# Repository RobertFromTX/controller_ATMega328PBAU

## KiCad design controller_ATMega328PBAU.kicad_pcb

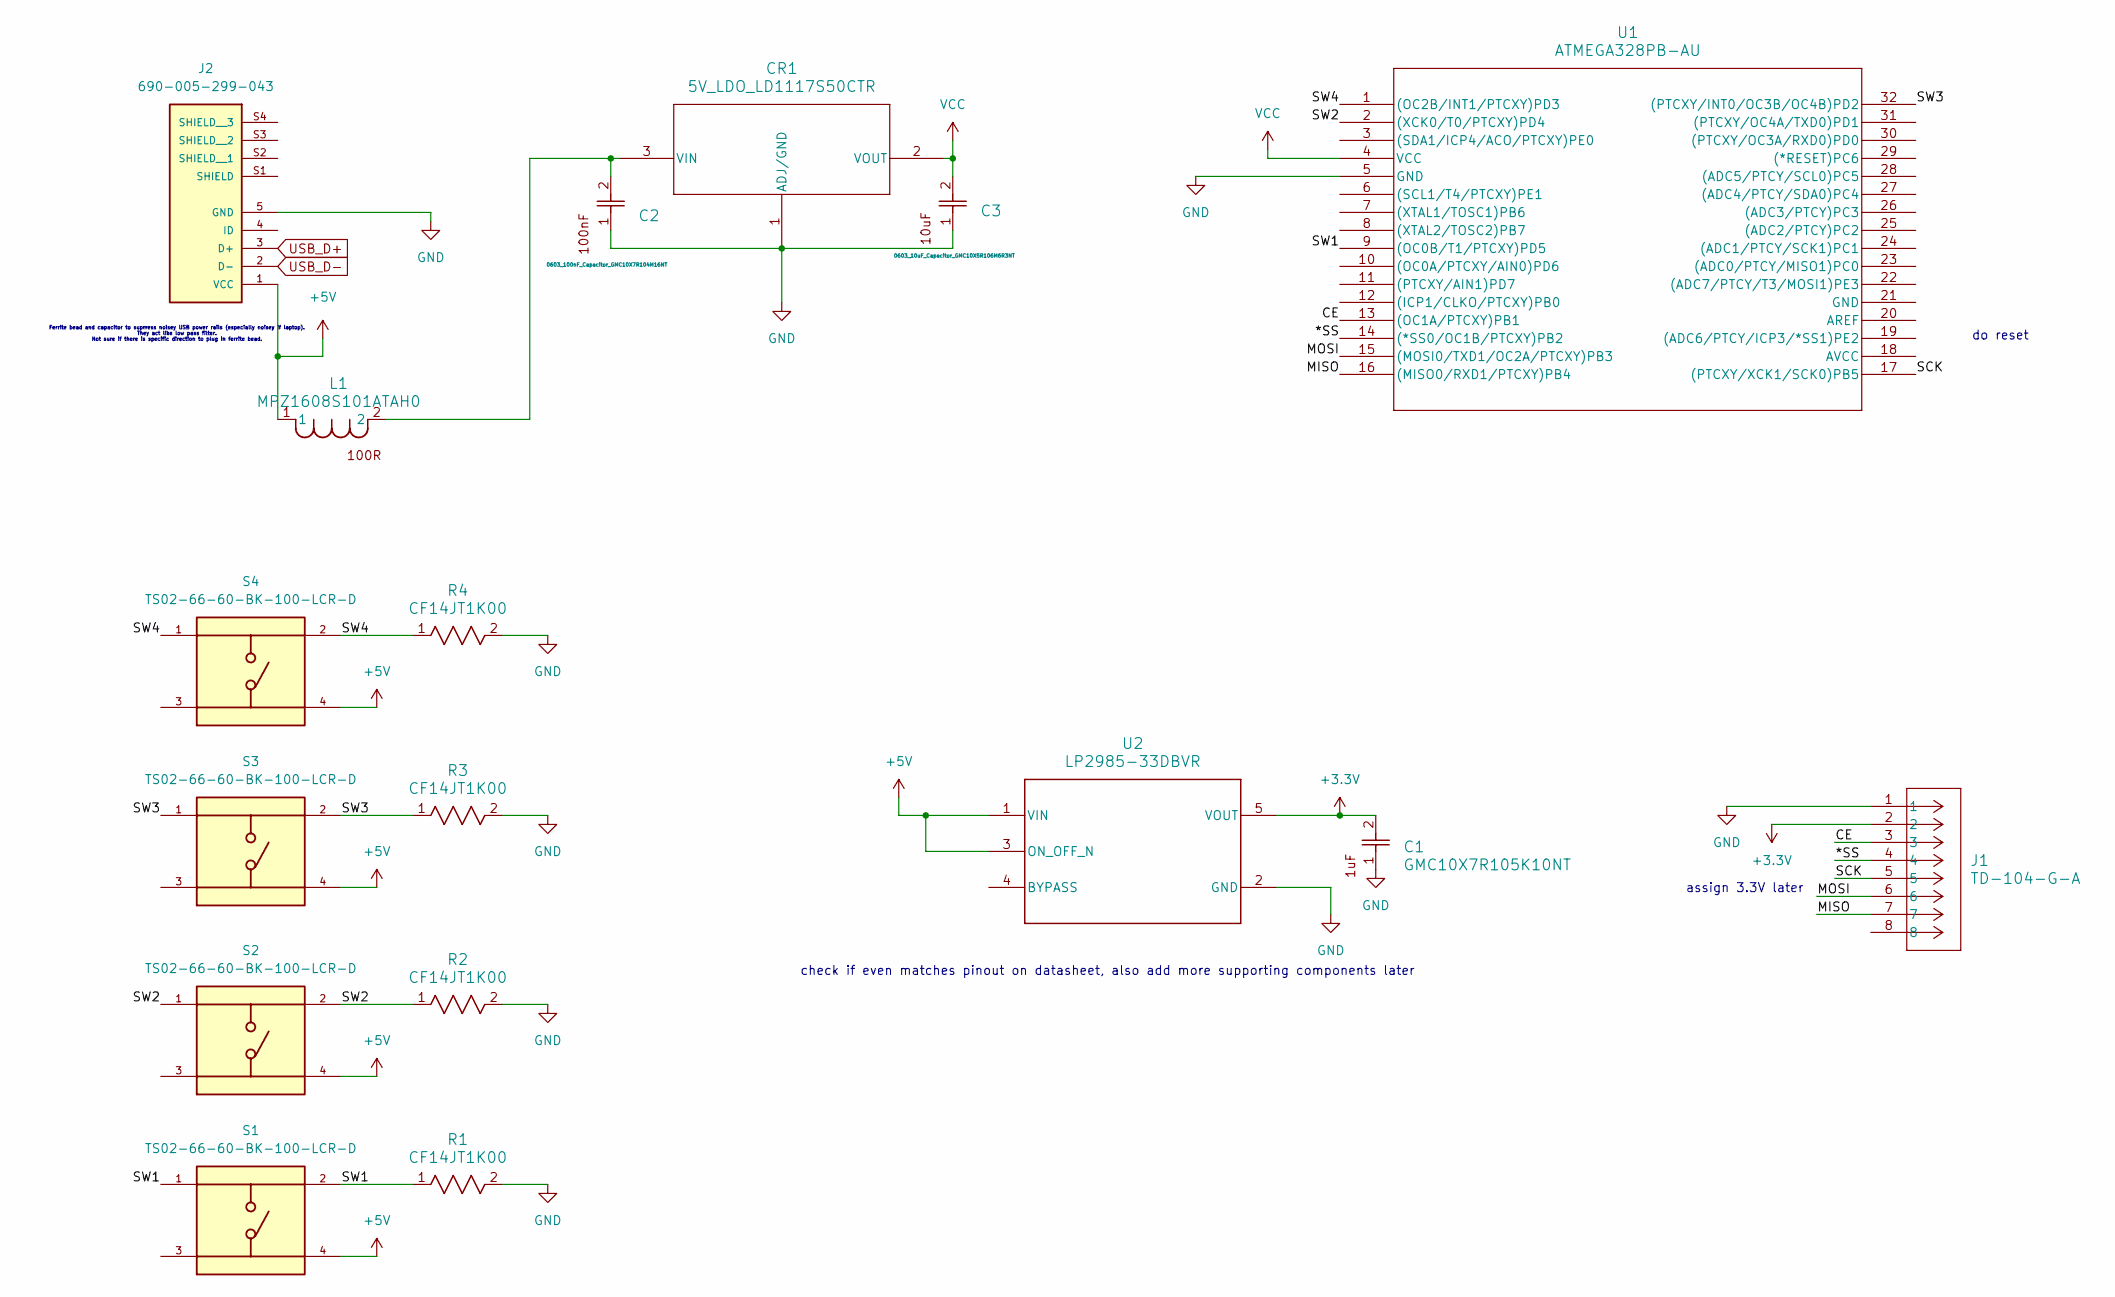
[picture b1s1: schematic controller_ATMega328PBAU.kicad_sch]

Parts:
C1: GMC10X7R105K10NT; CAP_GMC10_CCE
C2: 0603_100nF_Capacitor_GMC10X7R104M16NT; CAP_GMC10_CCE
C3: 0603_10uF_Capacitor_GMC10X5R106M6R3NT; CAP_GMC10_CCE
CR1: 5V_LDO_LD1117S50CTR; SOT-223_STM
J1: TD-104-G-A; CON8_2X4_TU_HTS_SAI
J2: 690-005-299-043; 690-005-299-043_EDAC_690-005-299-043; PARTREV 11
L1: MPZ1608S101ATAH0; IND_1608_TDK
R1, R2, R3, R4: CF14JT1K00; STA_CF14_STP
S1, S2, S3, S4: TS02-66-60-BK-100-LCR-D; SW_TS02-66-60-BK-100-LCR-D; PARTREV 1.0
U1: ATMEGA328PB-AU; 32A_MCH
U2: LP2985-33DBVR; DBV0005A_N

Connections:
+3.3V: C1.2, J1.2, U2.5 (VOUT)
+5V: J2.1 (VCC), L1.1, S1.4, S2.4, S3.4, S4.4, U2.1 (VIN), U2.3 (ON_OFF_N)
/*SS: J1.4, U1.14 ((*SS0/OC1B/PTCXY)PB2)
/CE: J1.3, U1.13 ((OC1A/PTCXY)PB1)
/MISO: J1.7, U1.16 ((MISO0/RXD1/PTCXY)PB4)
/MOSI: J1.6, U1.15 ((MOSI0/TXD1/OC2A/PTCXY)PB3)
/SCK: J1.5, U1.17 ((PTCXY/XCK1/SCK0)PB5)
/SW1: R1.1, S1.1, S1.2, U1.9 ((OC0B/T1/PTCXY)PD5)
/SW2: R2.1, S2.1, S2.2, U1.2 ((XCK0/T0/PTCXY)PD4)
/SW3: R3.1, S3.1, S3.2, U1.32 ((PTCXY/INT0/OC3B/OC4B)PD2)
/SW4: R4.1, S4.1, S4.2, U1.1 ((OC2B/INT1/PTCXY)PD3)
GND: C1.1, C2.1, C3.1, CR1.1 (ADJ/GND), J1.1, J2.5 (GND), R1.2, R2.2, R3.2, R4.2, U1.5 (GND), U2.2 (GND)
unnamed: C2.2, CR1.3 (VIN), L1.2
USB_D+: J2.3 (D+)
USB_D-: J2.2 (D-)
VCC: C3.2, CR1.2 (VOUT), U1.4 (VCC)

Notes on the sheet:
check if even matches pinout on datasheet, also add more supporting components later
assign 3.3V later
Ferrite bead and capacitor to suprress noisey USB power rails (especially noisey if laptop). They act like low pass filter. Not sure if there is specific direction to plug in ferrite bead.
do reset

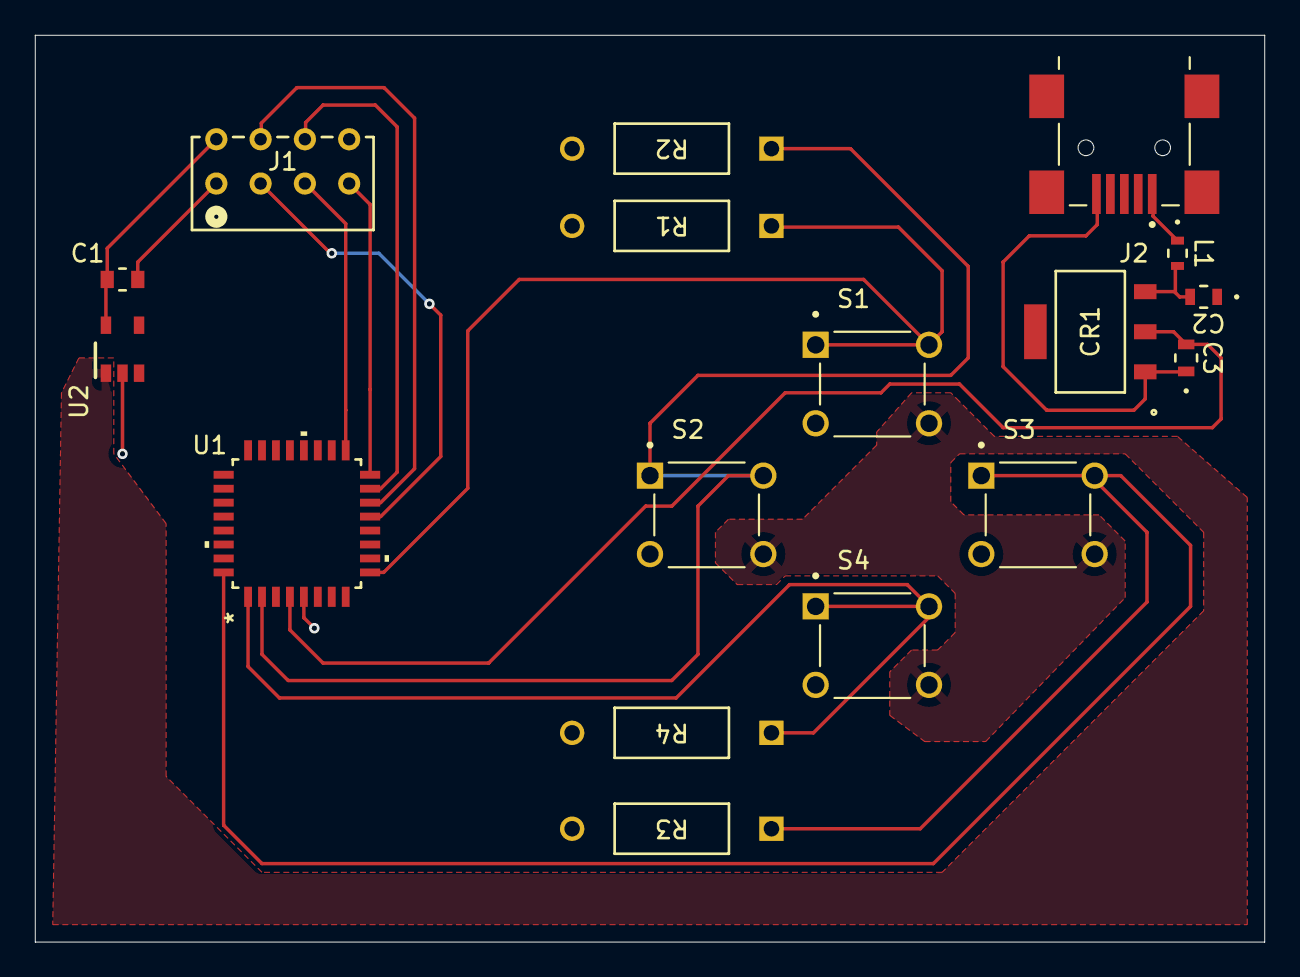
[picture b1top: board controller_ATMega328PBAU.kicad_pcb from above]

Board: 2 copper layers, 70.5 x 52.0 mm, 17 parts (0 on the bottom side), 14 nets.

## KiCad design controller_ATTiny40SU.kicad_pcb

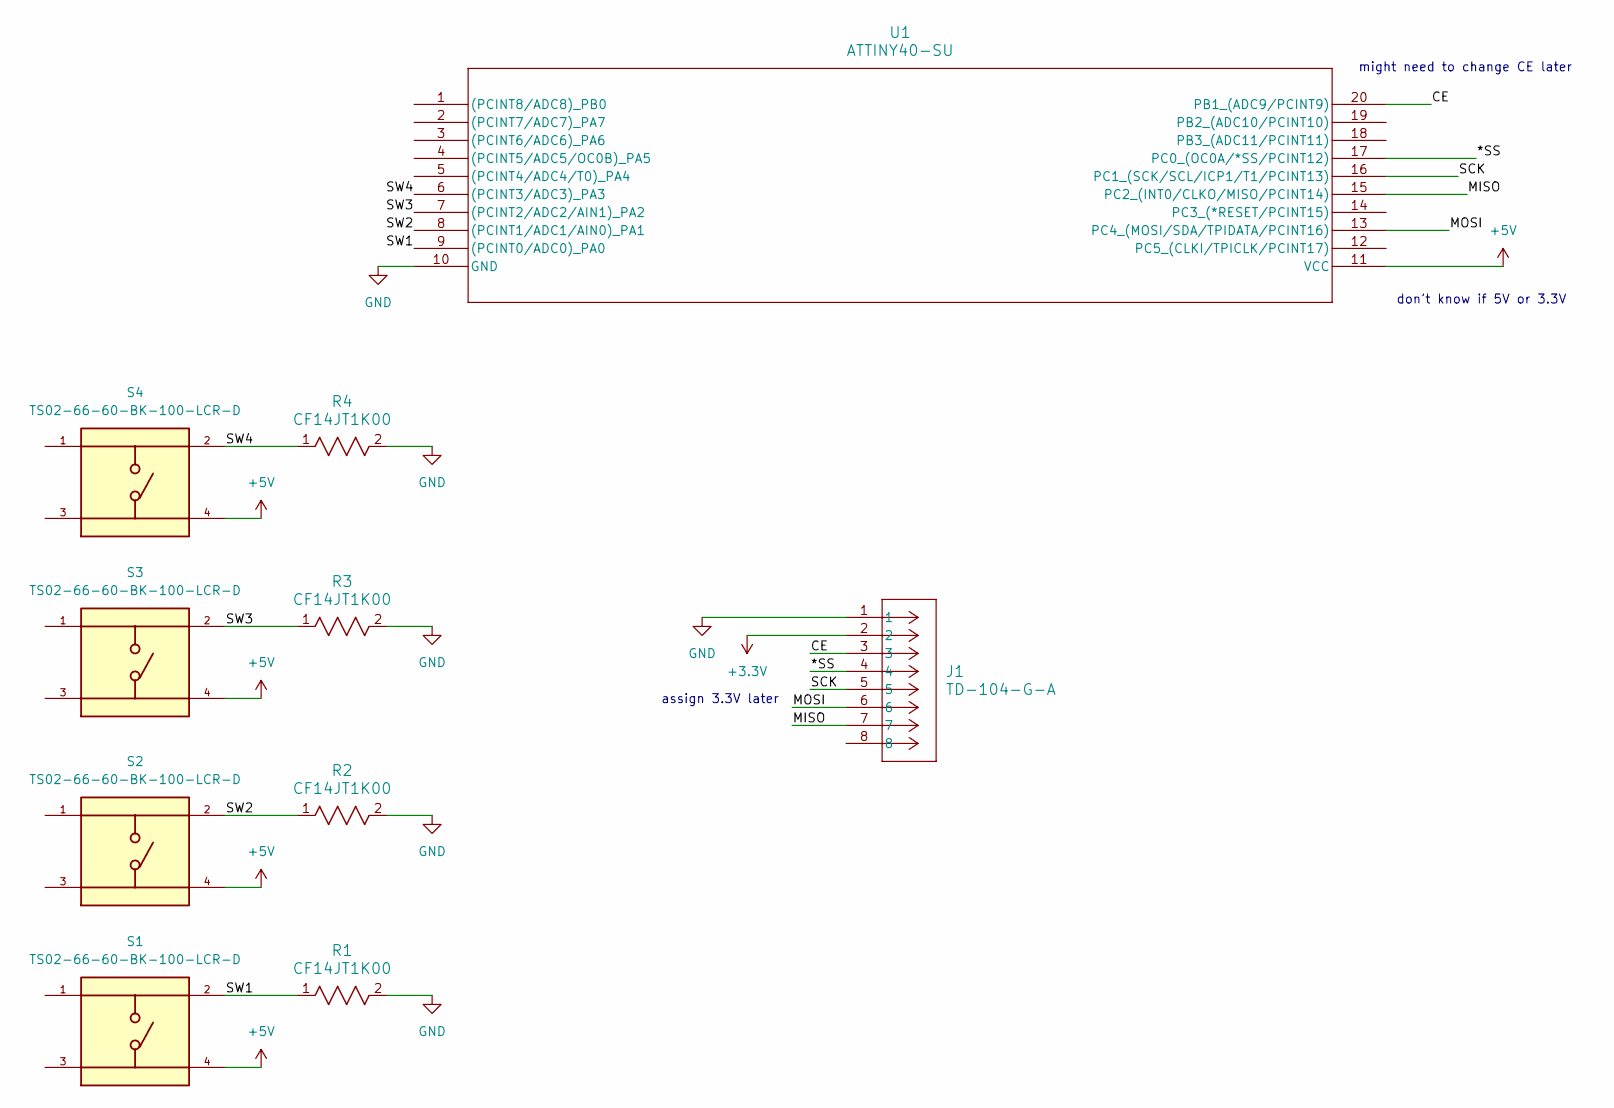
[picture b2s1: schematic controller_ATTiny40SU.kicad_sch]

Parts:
J1: TD-104-G-A; CON8_2X4_TU_HTS_SAI
R1, R2, R3, R4: CF14JT1K00; STA_CF14_STP
S1, S2, S3, S4: TS02-66-60-BK-100-LCR-D; SW_TS02-66-60-BK-100-LCR-D; PARTREV 1.0
U1: ATTINY40-SU; SOIC20-W_MC_MCH

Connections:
+3.3V: J1.2
+5V: S1.4, S2.4, S3.4, S4.4, U1.11 (VCC)
/*SS: J1.4, U1.17 (PC0_(OC0A/*SS/PCINT12))
/CE: J1.3, U1.20 (PB1_(ADC9/PCINT9))
/MISO: J1.7, U1.15 (PC2_(INT0/CLKO/MISO/PCINT14))
/MOSI: J1.6, U1.13 (PC4_(MOSI/SDA/TPIDATA/PCINT16))
/SCK: J1.5, U1.16 (PC1_(SCK/SCL/ICP1/T1/PCINT13))
/SW1: R1.1, S1.2, U1.9 ((PCINT0/ADC0)_PA0)
/SW2: R2.1, S2.2, U1.8 ((PCINT1/ADC1/AIN0)_PA1)
/SW3: R3.1, S3.2, U1.7 ((PCINT2/ADC2/AIN1)_PA2)
/SW4: R4.1, S4.2, U1.6 ((PCINT3/ADC3)_PA3)
GND: J1.1, R1.2, R2.2, R3.2, R4.2, U1.10 (GND)

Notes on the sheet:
might need to change CE later
assign 3.3V later
don't know if 5V or 3.3V

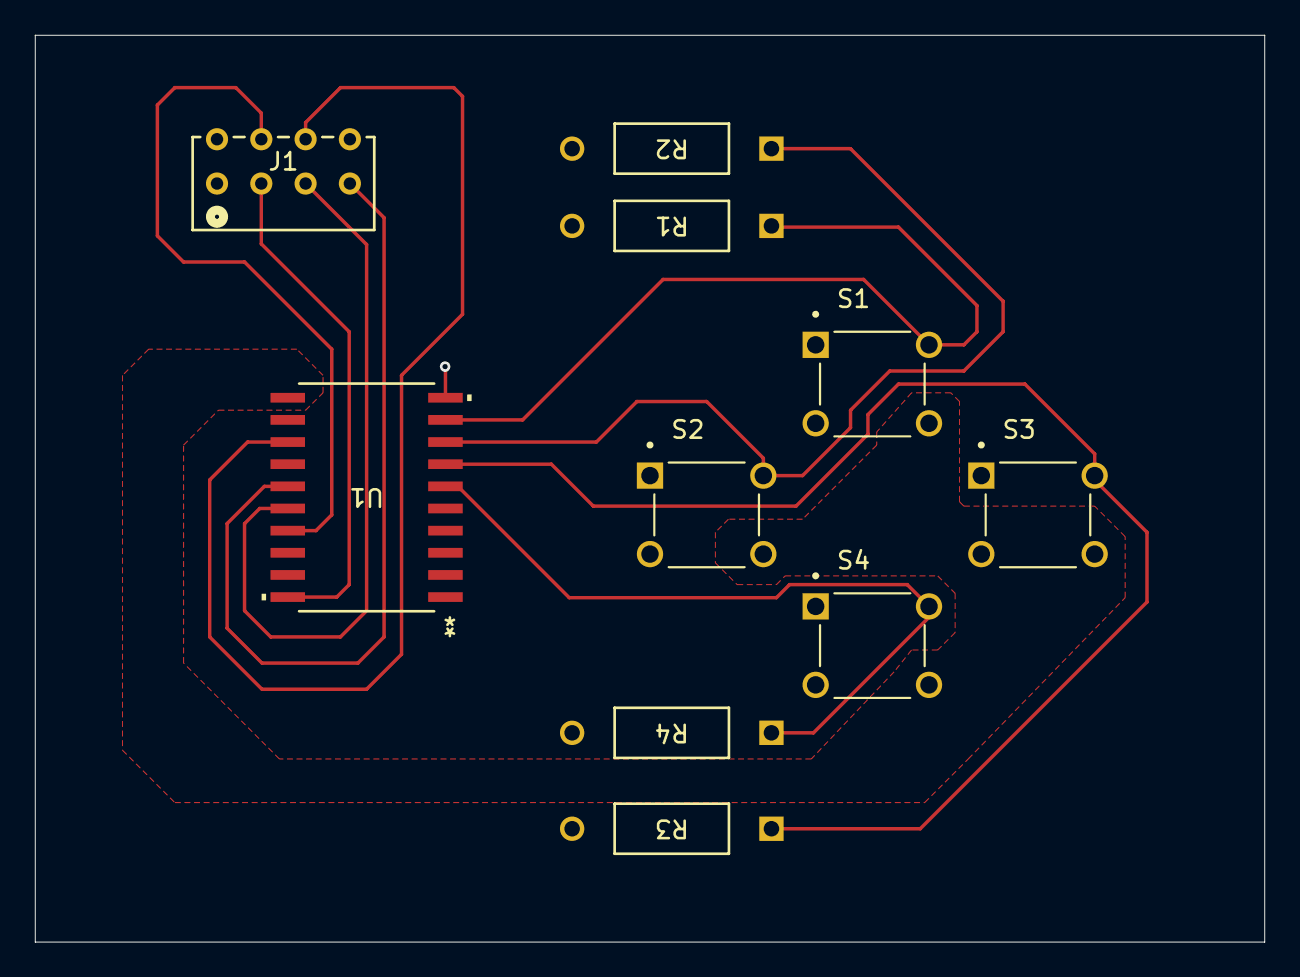
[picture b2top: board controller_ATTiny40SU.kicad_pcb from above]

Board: 2 copper layers, 70.5 x 52.0 mm, 10 parts (0 on the bottom side), 11 nets.

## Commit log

2024-10-17 added initial files
2024-10-19 change to atmega
2024-10-19 changed readme
